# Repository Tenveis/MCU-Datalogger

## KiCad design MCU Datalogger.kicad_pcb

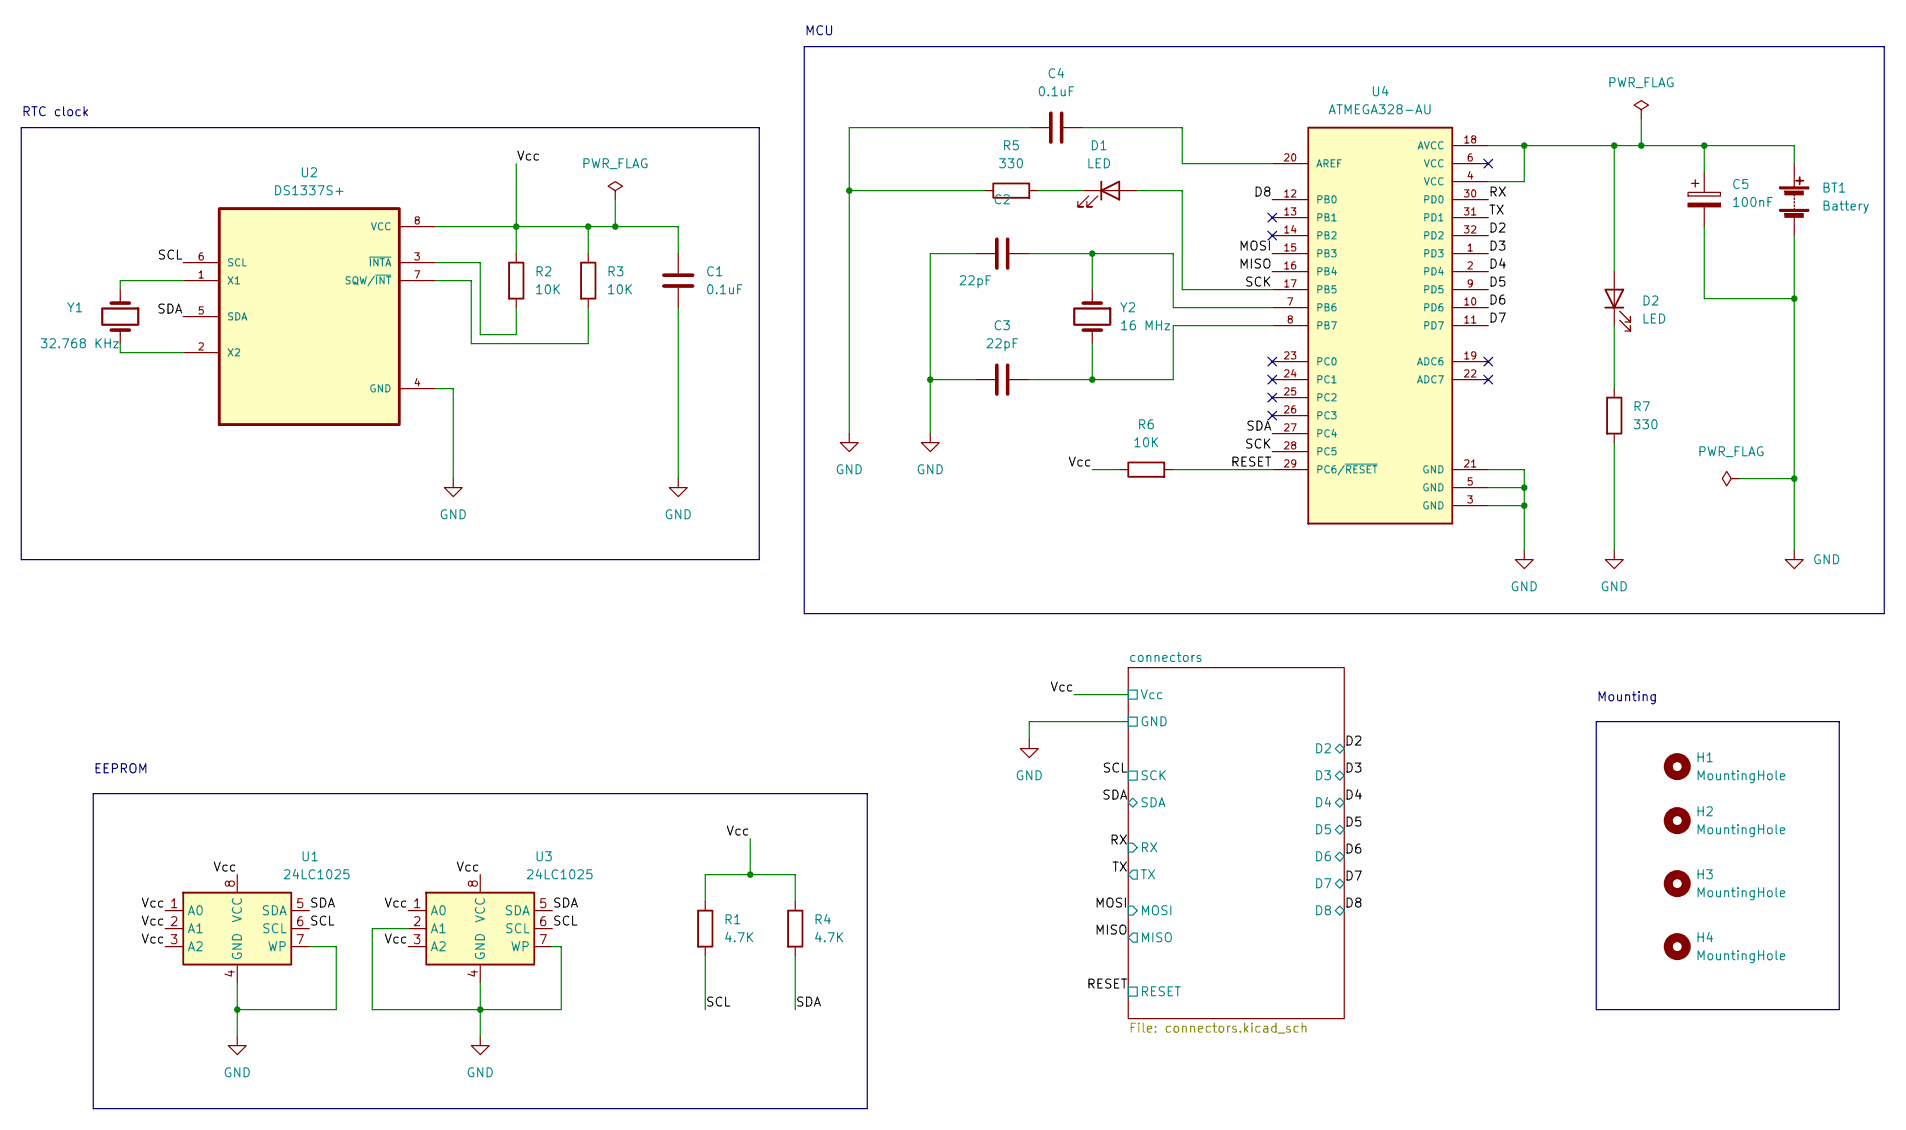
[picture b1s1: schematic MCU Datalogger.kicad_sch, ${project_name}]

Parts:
BT1: Battery; PinHeader_1x02_P2.54mm_Vertical
C1, C4: 0.1uF; C_0805_2012Metric
C2, C3: 22pF; C_0805_2012Metric
C5: 100nF; C_0805_2012Metric
D1, D2: LED; LED_0805_2012Metric
H1, H2, H3, H4: MountingHole; MountingHole_2.1mm
R1, R4: 4.7K; R_0805_2012Metric
R2, R3, R6: 10K; R_0805_2012Metric
R5, R7: 330; R_0805_2012Metric
U1, U3: 24LC1025; SOIC-8_5.23x5.23mm_P1.27mm
U2: DS1337S+; SOIC127P600X175-8N
U4: ATMEGA328-AU; QFP80P900X900X120-32N
Y1: 32.768 KHz; Crystal_SMD_5032-2Pin_5.0x3.2mm_HandSoldering
Y2: 16 MHz; Crystal_SMD_5032-2Pin_5.0x3.2mm_HandSoldering

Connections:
/D2: U4.32 (PD2); also elsewhere on the board
/D3: U4.1 (PD3); also elsewhere on the board
/D4: U4.2 (PD4); also elsewhere on the board
/D5: U4.9 (PD5); also elsewhere on the board
/D6: U4.10 (PD6); also elsewhere on the board
/D7: U4.11 (PD7); also elsewhere on the board
/D8: U4.12 (PB0); also elsewhere on the board
/MISO: U4.16 (PB4); also elsewhere on the board
/MOSI: U4.15 (PB3); also elsewhere on the board
/RESET: R6.2, U4.29 (PC6/~RESET); also elsewhere on the board
/RX: U4.30 (PD0); also elsewhere on the board
/SCK: D1.2 (A), U4.17 (PB5), U4.28 (PC5)
/SCL: R1.2, U1.6 (SCL), U2.6 (SCL), U3.6 (SCL); also elsewhere on the board
/SDA: R4.2, U1.5 (SDA), U2.5 (SDA), U3.5 (SDA), U4.27 (PC4); also elsewhere on the board
/TX: U4.31 (PD1); also elsewhere on the board
/Vcc: C1.1, R1.1, R2.1, R3.1, R4.1, R6.1, U1.1 (A0), U1.2 (A1), U1.3 (A2), U1.8 (VCC), U2.8 (VCC), U3.1 (A0), U3.3 (A2), U3.8 (VCC); also elsewhere on the board
GND: BT1.2 (-), C1.2, C2.1, C3.1, C4.1, C5.2, R5.1, R7.2, U1.4 (GND), U1.7 (WP), U2.4 (GND), U3.2 (A1), U3.4 (GND), U3.7 (WP), U4.3 (GND), U4.5 (GND), U4.21 (GND); also elsewhere on the board
unnamed: BT1.1 (+), C5.1, D2.2 (A), U4.4 (VCC), U4.18 (AVCC)
unnamed: C2.2, U4.7 (PB6), Y2.1
unnamed: C3.2, U4.8 (PB7), Y2.2
unnamed: C4.2, U4.20 (AREF)
unnamed: D1.1 (K), R5.2
unnamed: D2.1 (K), R7.1
unnamed: R2.2, U2.3 (~INTA)
unnamed: R3.2, U2.7 (SQW/~INT)
unnamed: U2.1 (X1), Y1.1
unnamed: U2.2 (X2), Y1.2

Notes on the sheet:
EEPROM
MCU
Mounting
RTC clock

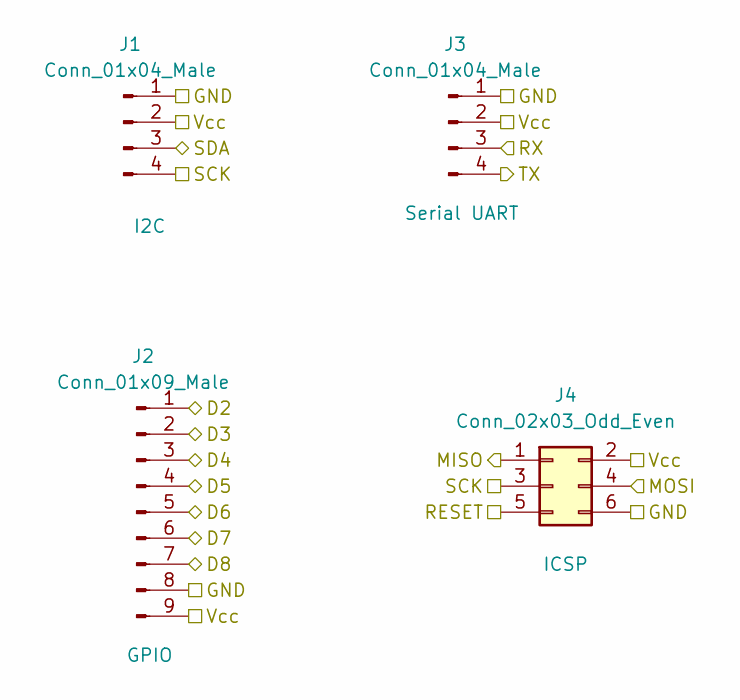
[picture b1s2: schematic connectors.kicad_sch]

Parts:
J1, J3: Conn_01x04_Male; PinHeader_1x04_P2.54mm_Vertical
J2: Conn_01x09_Male; PinHeader_1x09_P2.54mm_Vertical
J4: Conn_02x03_Odd_Even; PinHeader_2x03_P2.54mm_Vertical

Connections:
/D2: J2.1; also elsewhere on the board
/D3: J2.2; also elsewhere on the board
/D4: J2.3; also elsewhere on the board
/D5: J2.4; also elsewhere on the board
/D6: J2.5; also elsewhere on the board
/D7: J2.6; also elsewhere on the board
/D8: J2.7; also elsewhere on the board
/MISO: J4.1; also elsewhere on the board
/MOSI: J4.4; also elsewhere on the board
/RESET: J4.5; also elsewhere on the board
/RX: J3.3; also elsewhere on the board
/SCL: J1.4, J4.3; also elsewhere on the board
/SDA: J1.3; also elsewhere on the board
/TX: J3.4; also elsewhere on the board
/Vcc: J1.2, J2.9, J3.2, J4.2; also elsewhere on the board
GND: J1.1, J2.8, J3.1, J4.6; also elsewhere on the board

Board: 2 copper layers, 29 parts (0 on the bottom side), 27 nets, no tracks yet.

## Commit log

2022-09-23 Initial comment of Project
2022-09-23 Symbols have been added to the Sheet
2022-09-23 Place the symbols at relevent place.(Arrange) and Annote them.
2022-09-23 Added component(symbol) Values.
2022-09-23 Done with the symbol-footprint associations
2022-09-23 Completed the wiring of main sheet.
2022-09-23 Completed the wiring of Connectors sheet(2). PS: No ERC error.
2022-09-23 assign GND & Vcc to Net Class (Power).
2022-09-23 ERC done. No errors/warning found.
2022-09-23 Complete with adding comments in the sheet.
2022-09-24 Setup PCB Editor, Import all the components.
2022-09-24 Bug resolved: add Vcc net to MC.
